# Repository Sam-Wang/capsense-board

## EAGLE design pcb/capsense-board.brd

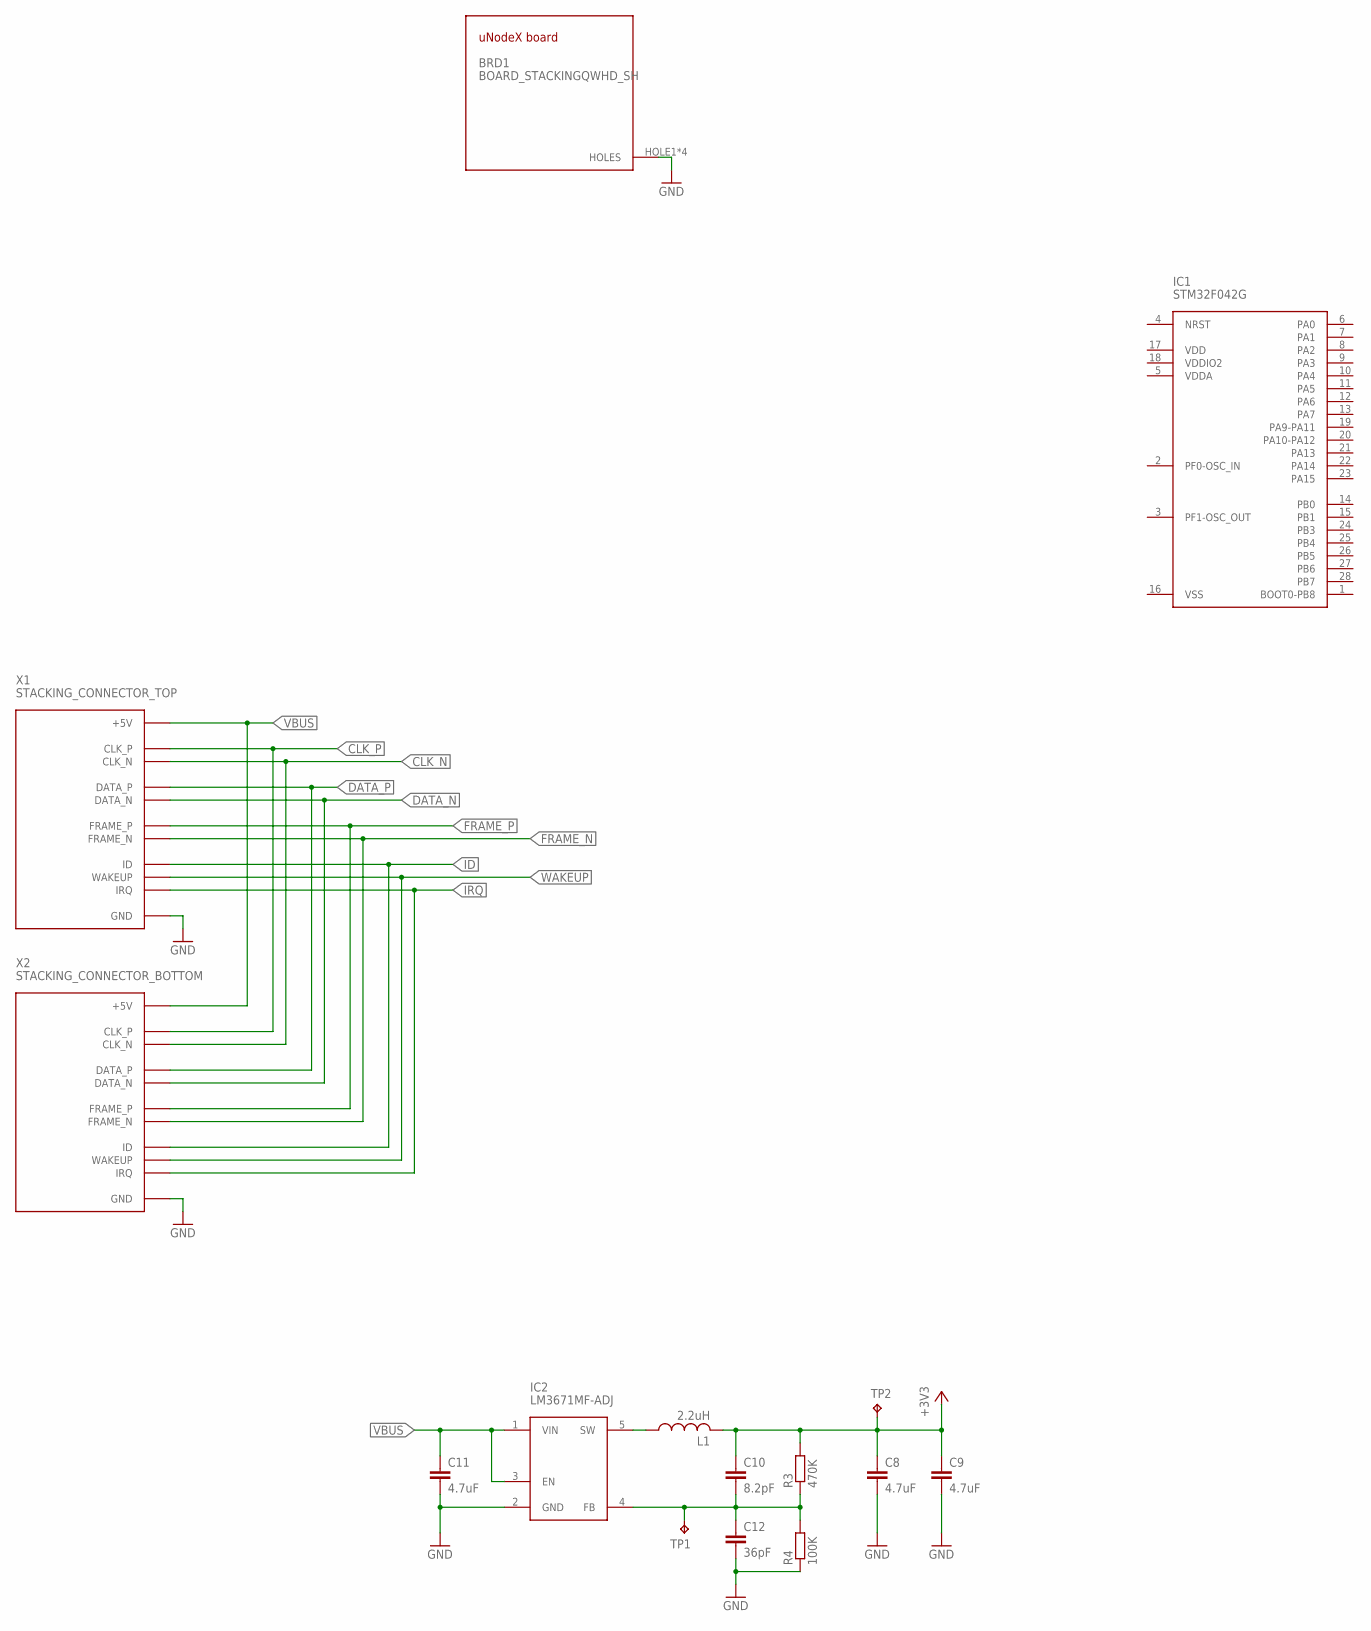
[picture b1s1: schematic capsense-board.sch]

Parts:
BRD1: BOARD_STACKINGQWHD_SH; QWHD_SHARP_CORNERS
C8, C9, C11: 4.7uF; C0805
C10: 8.2pF; C0603
C12: 36pF; C0603
IC1: STM32F042G; UFQFPN28
IC2: LM3671MF-ADJ; SOT23-5
L1: 2.2uH; L2012C
R3: 470K; R0603
R4: 100K; R0603
TP1, TP2: TPB1,27; B1,27
X1: STACKING_CONNECTOR_TOP; HAR-FLEX-TOP-12P
X2: STACKING_CONNECTOR_BOTTOM; HAR-FLEX-BOTTOM-12P

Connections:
+3V3: C8.1, C9.1, C10.1, L1.2, R3.2, TP2.TP
CLK_N: X1.CLK_N, X2.CLK_N
CLK_P: X1.CLK_P, X2.CLK_P
DATA_N: X1.DATA_N, X2.DATA_N
DATA_P: X1.DATA_P, X2.DATA_P
FRAME_N: X1.FRAME_N, X2.FRAME_N
FRAME_P: X1.FRAME_P, X2.FRAME_P
GND: BRD1.HOLE1, BRD1.HOLE2, BRD1.HOLE3, BRD1.HOLE4, C8.2, C9.2, C11.2, C12.2, IC2.2 (GND), R4.1, X1.GND1 (GND), X1.GND2 (GND), X1.H1 (GND), X1.H2 (GND), X1.H3 (GND), X1.H4 (GND), X2.GND1 (GND), X2.GND2 (GND), X2.H1 (GND), X2.H2 (GND), X2.H3 (GND), X2.H4 (GND)
ID: X1.ID, X2.ID
IRQ: X1.IRQ, X2.IRQ
unnamed: IC2.5 (SW), L1.1
unnamed: C10.2, C12.1, IC2.4 (FB), R3.1, R4.2, TP1.TP
VBUS: C11.1, IC2.1 (VIN), IC2.3 (EN), X1.+5V, X2.+5V
WAKEUP: X1.WAKEUP, X2.WAKEUP

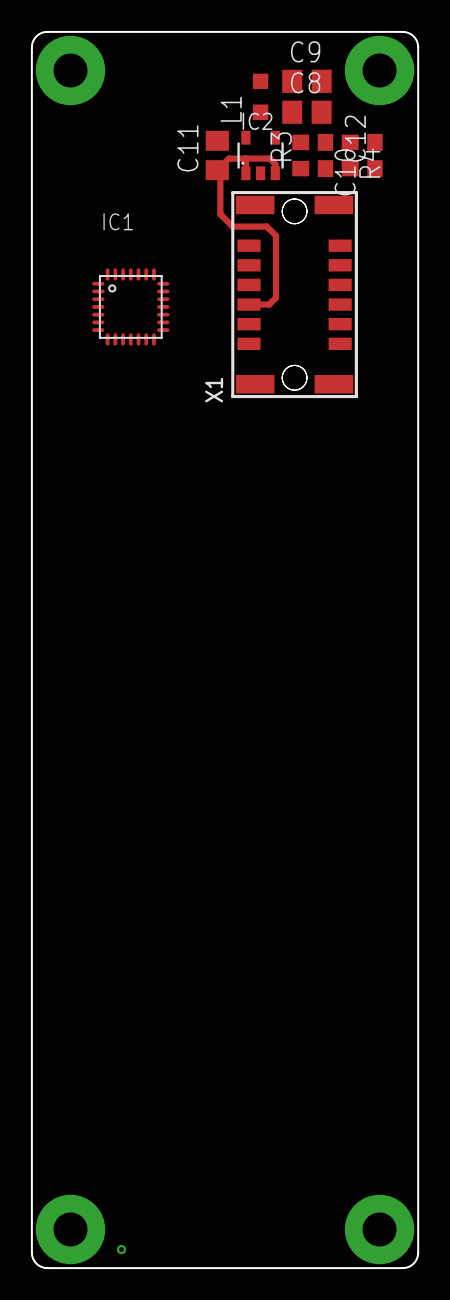
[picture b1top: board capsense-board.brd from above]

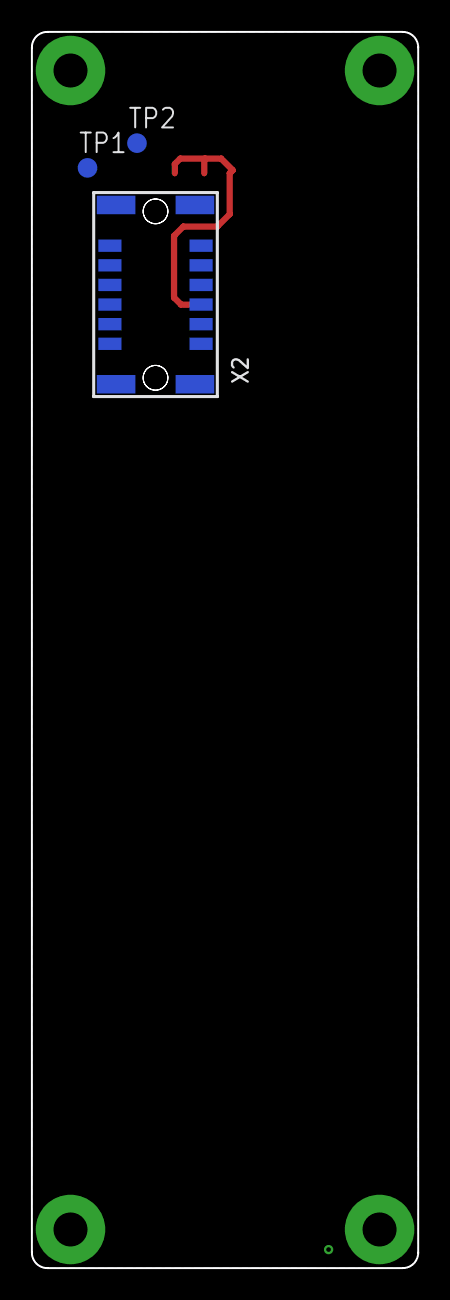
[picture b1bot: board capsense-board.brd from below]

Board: 2 copper layers, 25.0 x 80.0 mm, 15 parts (2 on the bottom side), 14 nets.

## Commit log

2017-03-19 Add uNodeX board layout and bus connectors
